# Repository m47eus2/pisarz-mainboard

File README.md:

# pisarz-mainboard
Mainboard for PiSARZ project

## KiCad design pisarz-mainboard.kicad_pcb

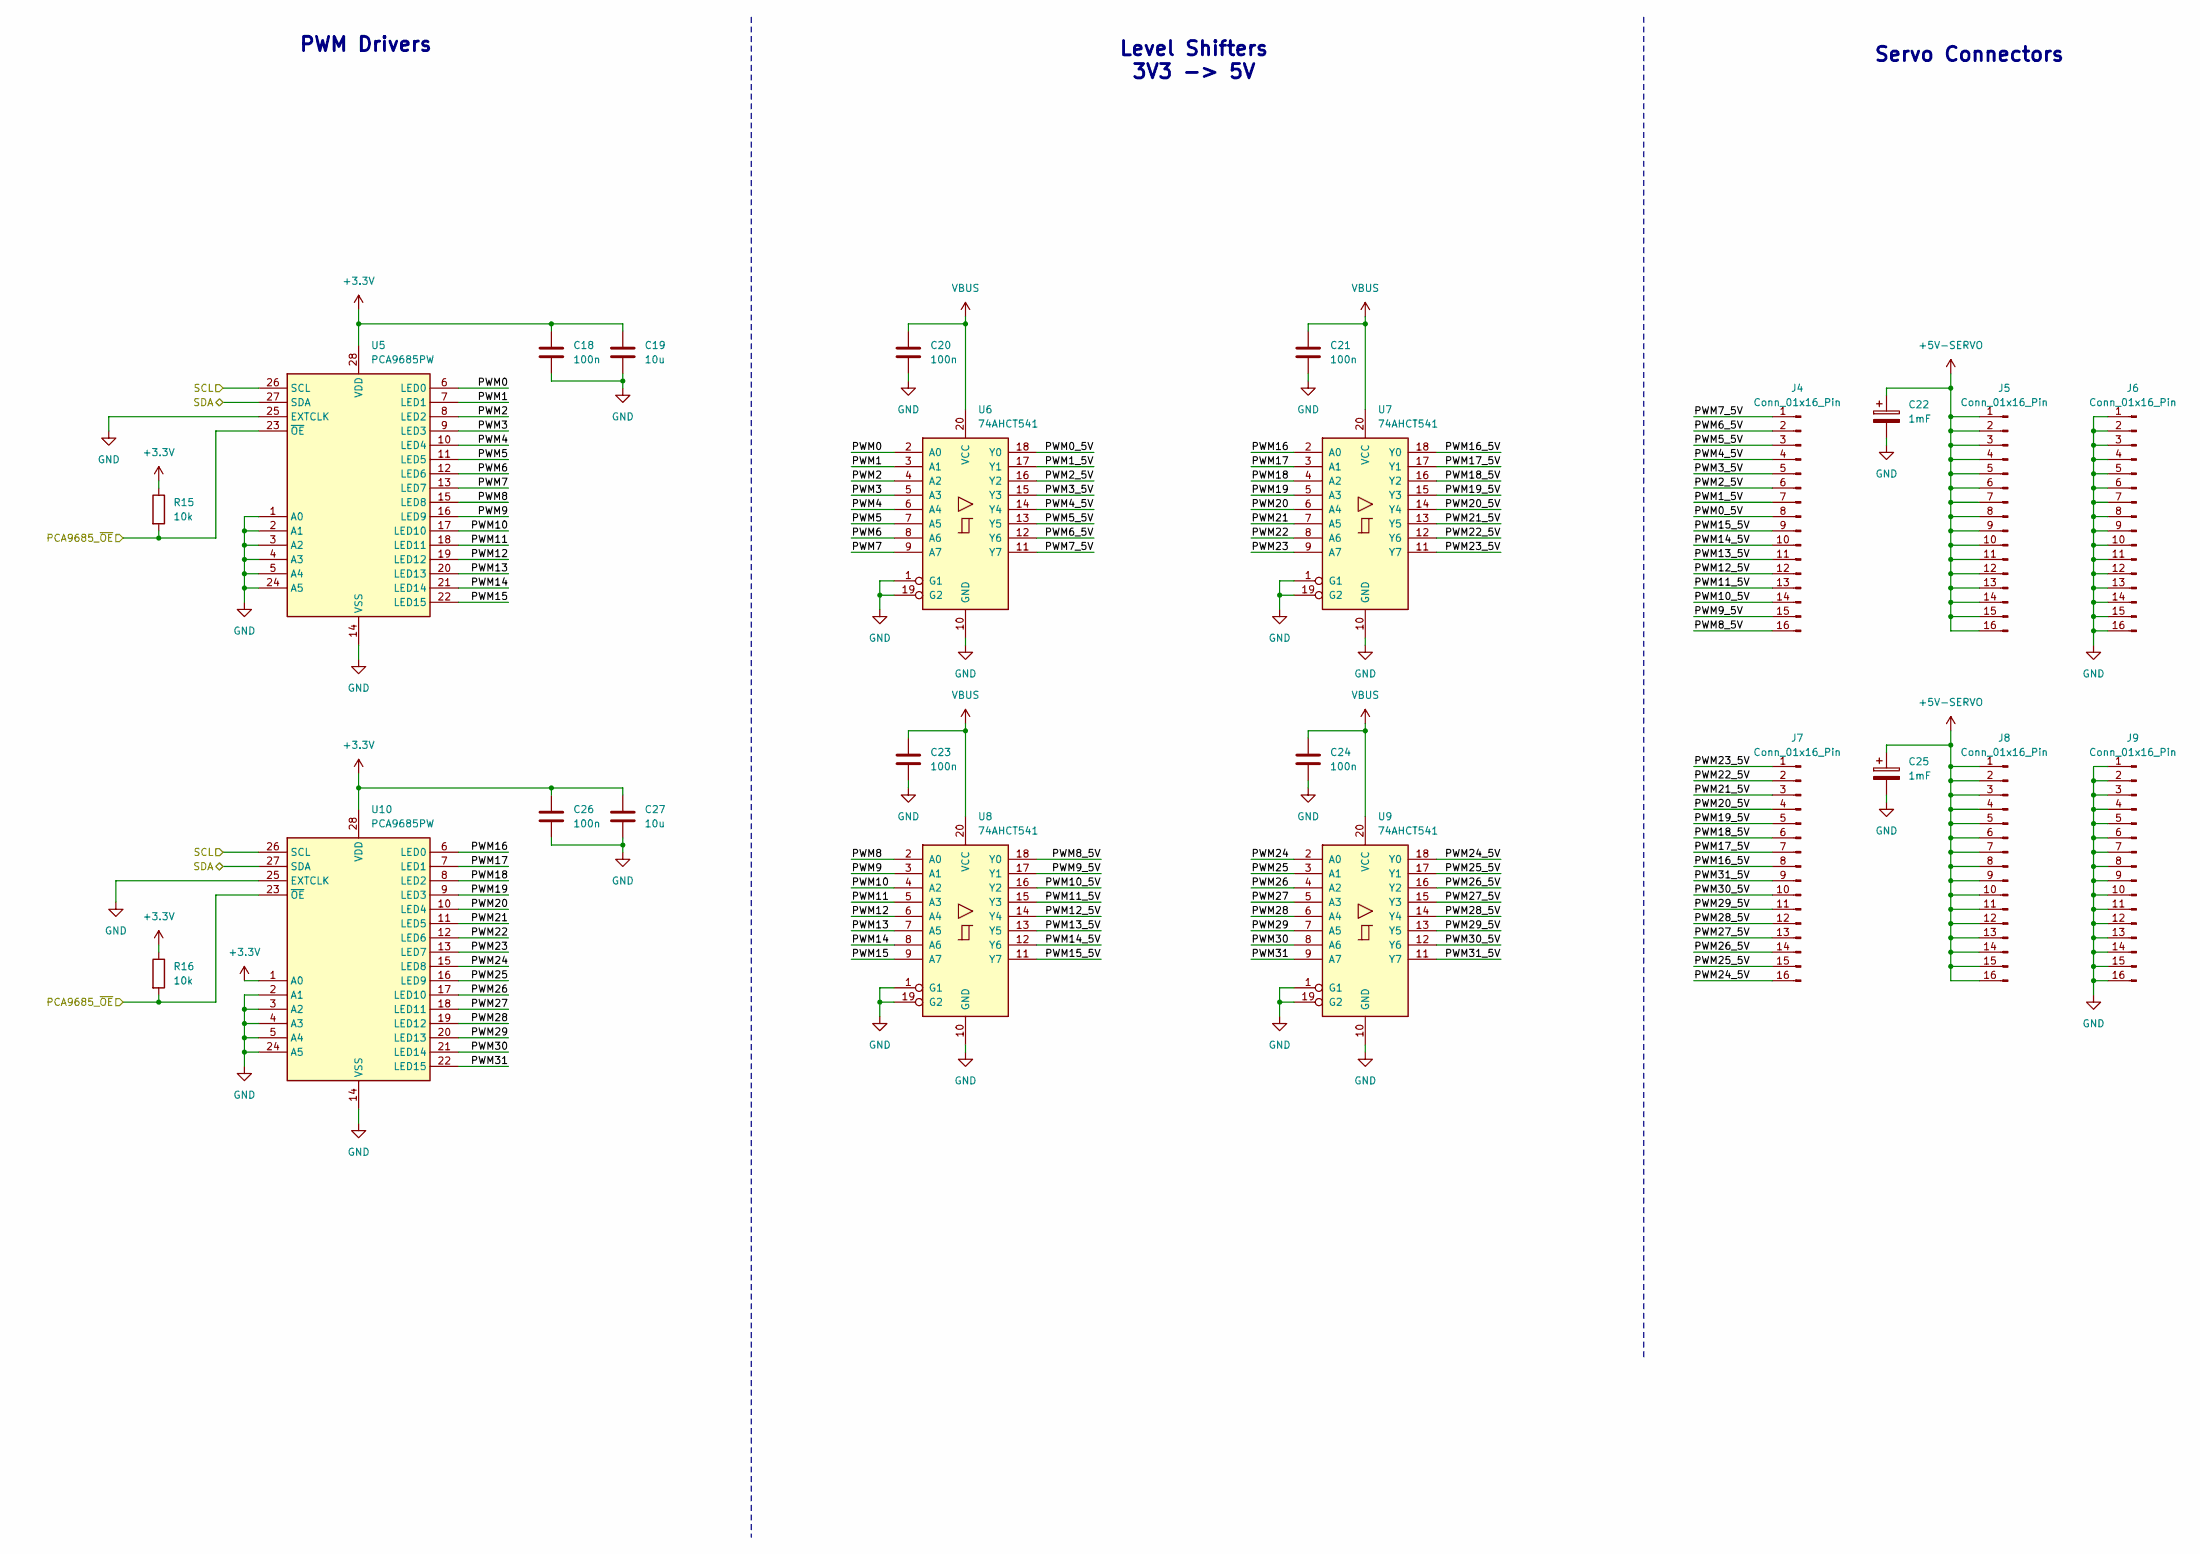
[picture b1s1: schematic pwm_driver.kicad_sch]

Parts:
C18, C20, C21, C23, C24, C26: 100n; C_0402_1005Metric_Pad0.74x0.62mm_HandSolder
C19, C27: 10u; C_0805_2012Metric_Pad1.18x1.45mm_HandSolder
C22, C25: 1mF; CP_Radial_D8.0mm_P3.50mm
J4, J5, J6, J7, J8, J9: Conn_01x16_Pin; PinHeader_1x16_P2.54mm_Vertical
R15, R16: 10k; R_0402_1005Metric_Pad0.72x0.64mm_HandSolder
U5, U10: PCA9685PW; TSSOP-28_4.4x9.7mm_P0.65mm
U6, U7, U8, U9: 74AHCT541; SSOP-20_4.4x6.5mm_P0.65mm

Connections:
+3.3V: C18.1, C19.1, C26.1, C27.1, R15.1, R16.1, U5.28 (VDD), U10.1 (A0), U10.28 (VDD); also elsewhere on the board
+5V-SERVO: C22.1, C25.1, J5.1, J5.2, J5.3, J5.4, J5.5, J5.6, J5.7, J5.8, J5.9, J5.10, J5.11, J5.12, J5.13, J5.14, J5.15, J5.16, J8.1, J8.2, J8.3, J8.4, J8.5, J8.6, J8.7, J8.8, J8.9, J8.10, J8.11, J8.12, J8.13, J8.14, J8.15, J8.16; also elsewhere on the board
/mcu/I2C_SCL: U5.26 (SCL), U10.26 (SCL); also elsewhere on the board
/mcu/I2C_SDA: U5.27 (SDA), U10.27 (SDA); also elsewhere on the board
/mcu/PCA_OE: R15.2, R16.2, U5.23 (~OE), U10.23 (~OE); also elsewhere on the board
/pwm-driver/PWM0: U5.6 (LED0), U6.2 (A0)
/pwm-driver/PWM0_5V: J4.8, U6.18 (Y0)
/pwm-driver/PWM1: U5.7 (LED1), U6.3 (A1)
/pwm-driver/PWM1_5V: J4.7, U6.17 (Y1)
/pwm-driver/PWM2: U5.8 (LED2), U6.4 (A2)
/pwm-driver/PWM2_5V: J4.6, U6.16 (Y2)
/pwm-driver/PWM3: U5.9 (LED3), U6.5 (A3)
/pwm-driver/PWM3_5V: J4.5, U6.15 (Y3)
/pwm-driver/PWM4: U5.10 (LED4), U6.6 (A4)
/pwm-driver/PWM4_5V: J4.4, U6.14 (Y4)
/pwm-driver/PWM5: U5.11 (LED5), U6.7 (A5)
/pwm-driver/PWM5_5V: J4.3, U6.13 (Y5)
/pwm-driver/PWM6: U5.12 (LED6), U6.8 (A6)
/pwm-driver/PWM6_5V: J4.2, U6.12 (Y6)
/pwm-driver/PWM7: U5.13 (LED7), U6.9 (A7)
/pwm-driver/PWM7_5V: J4.1, U6.11 (Y7)
/pwm-driver/PWM8: U5.15 (LED8), U8.2 (A0)
/pwm-driver/PWM8_5V: J4.16, U8.18 (Y0)
/pwm-driver/PWM9: U5.16 (LED9), U8.3 (A1)
/pwm-driver/PWM9_5V: J4.15, U8.17 (Y1)
/pwm-driver/PWM10: U5.17 (LED10), U8.4 (A2)
/pwm-driver/PWM10_5V: J4.14, U8.16 (Y2)
/pwm-driver/PWM11: U5.18 (LED11), U8.5 (A3)
/pwm-driver/PWM11_5V: J4.13, U8.15 (Y3)
/pwm-driver/PWM12: U5.19 (LED12), U8.6 (A4)
/pwm-driver/PWM12_5V: J4.12, U8.14 (Y4)
/pwm-driver/PWM13: U5.20 (LED13), U8.7 (A5)
/pwm-driver/PWM13_5V: J4.11, U8.13 (Y5)
/pwm-driver/PWM14: U5.21 (LED14), U8.8 (A6)
/pwm-driver/PWM14_5V: J4.10, U8.12 (Y6)
/pwm-driver/PWM15: U5.22 (LED15), U8.9 (A7)
/pwm-driver/PWM15_5V: J4.9, U8.11 (Y7)
/pwm-driver/PWM16: U7.2 (A0), U10.6 (LED0)
/pwm-driver/PWM16_5V: J7.8, U7.18 (Y0)
/pwm-driver/PWM17: U7.3 (A1), U10.7 (LED1)
/pwm-driver/PWM17_5V: J7.7, U7.17 (Y1)
/pwm-driver/PWM18: U7.4 (A2), U10.8 (LED2)
/pwm-driver/PWM18_5V: J7.6, U7.16 (Y2)
/pwm-driver/PWM19: U7.5 (A3), U10.9 (LED3)
/pwm-driver/PWM19_5V: J7.5, U7.15 (Y3)
/pwm-driver/PWM20: U7.6 (A4), U10.10 (LED4)
/pwm-driver/PWM20_5V: J7.4, U7.14 (Y4)
/pwm-driver/PWM21: U7.7 (A5), U10.11 (LED5)
/pwm-driver/PWM21_5V: J7.3, U7.13 (Y5)
/pwm-driver/PWM22: U7.8 (A6), U10.12 (LED6)
/pwm-driver/PWM22_5V: J7.2, U7.12 (Y6)
/pwm-driver/PWM23: U7.9 (A7), U10.13 (LED7)
/pwm-driver/PWM23_5V: J7.1, U7.11 (Y7)
/pwm-driver/PWM24: U9.2 (A0), U10.15 (LED8)
/pwm-driver/PWM24_5V: J7.16, U9.18 (Y0)
/pwm-driver/PWM25: U9.3 (A1), U10.16 (LED9)
/pwm-driver/PWM25_5V: J7.15, U9.17 (Y1)
/pwm-driver/PWM26: U9.4 (A2), U10.17 (LED10)
/pwm-driver/PWM26_5V: J7.14, U9.16 (Y2)
/pwm-driver/PWM27: U9.5 (A3), U10.18 (LED11)
/pwm-driver/PWM27_5V: J7.13, U9.15 (Y3)
/pwm-driver/PWM28: U9.6 (A4), U10.19 (LED12)
/pwm-driver/PWM28_5V: J7.12, U9.14 (Y4)
/pwm-driver/PWM29: U9.7 (A5), U10.20 (LED13)
/pwm-driver/PWM29_5V: J7.11, U9.13 (Y5)
/pwm-driver/PWM30: U9.8 (A6), U10.21 (LED14)
/pwm-driver/PWM30_5V: J7.10, U9.12 (Y6)
/pwm-driver/PWM31: U9.9 (A7), U10.22 (LED15)
/pwm-driver/PWM31_5V: J7.9, U9.11 (Y7)
GND: C18.2, C19.2, C20.2, C21.2, C22.2, C23.2, C24.2, C25.2, C26.2, C27.2, J6.1, J6.2, J6.3, J6.4, J6.5, J6.6, J6.7, J6.8, J6.9, J6.10, J6.11, J6.12, J6.13, J6.14, J6.15, J6.16, J9.1, J9.2, J9.3, J9.4, J9.5, J9.6, J9.7, J9.8, J9.9, J9.10, J9.11, J9.12, J9.13, J9.14, J9.15, J9.16, U5.1 (A0), U5.2 (A1), U5.3 (A2), U5.4 (A3), U5.5 (A4), U5.14 (VSS), U5.24 (A5), U5.25 (EXTCLK), U6.1 (G1), U6.10 (GND), U6.19 (G2), U7.1 (G1), U7.10 (GND), U7.19 (G2), U8.1 (G1), U8.10 (GND), U8.19 (G2), U9.1 (G1), U9.10 (GND), U9.19 (G2), U10.2 (A1), U10.3 (A2), U10.4 (A3), U10.5 (A4), U10.14 (VSS), U10.24 (A5), U10.25 (EXTCLK); also elsewhere on the board
VBUS: C20.1, C21.1, C23.1, C24.1, U6.20 (VCC), U7.20 (VCC), U8.20 (VCC), U9.20 (VCC); also elsewhere on the board

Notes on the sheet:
Level Shifters 3V3 -> 5V
PWM Drivers
Servo Connectors

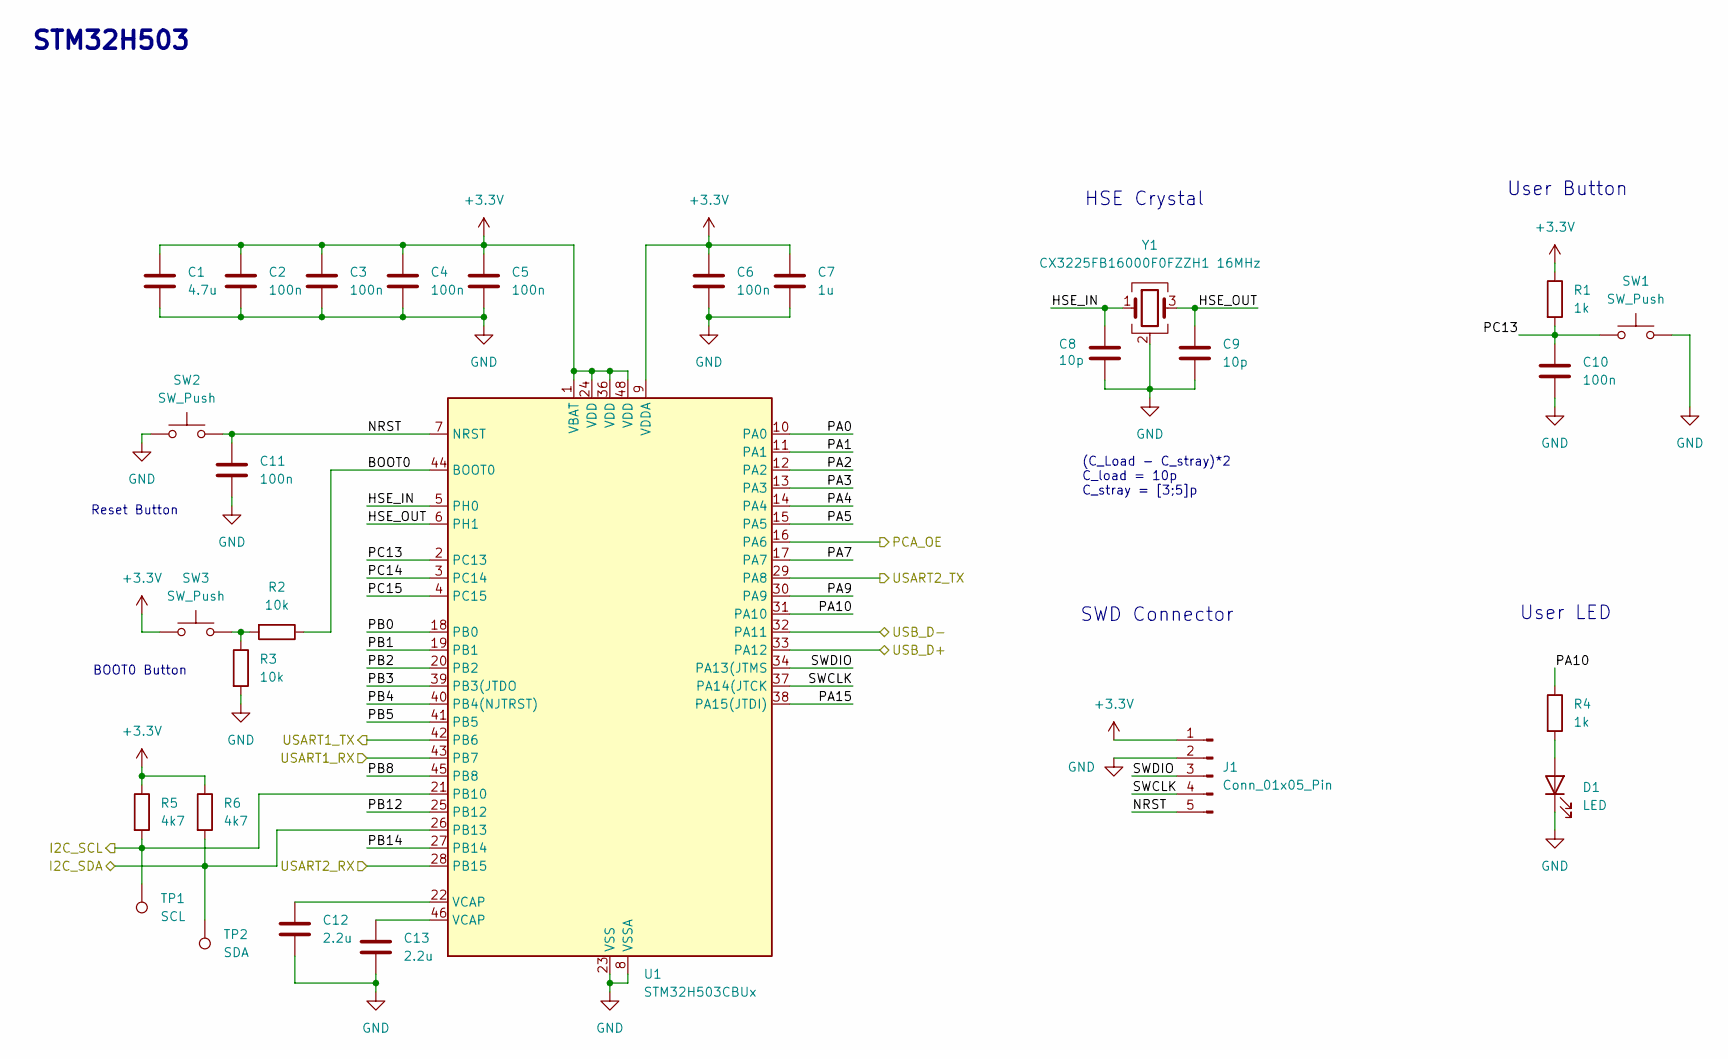
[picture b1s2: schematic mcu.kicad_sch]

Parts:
C1: 4.7u; C_0805_2012Metric_Pad1.18x1.45mm_HandSolder
C2, C3, C4, C5, C6, C10, C11: 100n; C_0402_1005Metric_Pad0.74x0.62mm_HandSolder
C7: 1u; C_0603_1608Metric_Pad1.08x0.95mm_HandSolder
C8, C9: 10p; C_0402_1005Metric_Pad0.74x0.62mm_HandSolder
C12, C13: 2.2u; C_0603_1608Metric_Pad1.08x0.95mm_HandSolder
D1: LED; LED_0805_2012Metric_Pad1.15x1.40mm_HandSolder
J1: Conn_01x05_Pin; PinHeader_1x05_P2.54mm_Vertical
R1, R4: 1k; R_0402_1005Metric_Pad0.72x0.64mm_HandSolder
R2, R3: 10k; R_0402_1005Metric_Pad0.72x0.64mm_HandSolder
R5, R6: 4k7; R_0402_1005Metric_Pad0.72x0.64mm_HandSolder
SW1, SW2, SW3: SW_Push; SW_Push_1P1T_NO_E-Switch_TL3301NxxxxxG
TP1: SCL; TestPoint_Pad_D1.0mm
TP2: SDA; TestPoint_Pad_D1.0mm
U1: STM32H503CBUx; QFN-48-1EP_7x7mm_P0.5mm_EP5.6x5.6mm
Y1: CX3225FB16000F0FZZH1 16MHz; Crystal_SMD_3225-4Pin_3.2x2.5mm

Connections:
+3.3V: C1.1, C2.1, C3.1, C4.1, C5.1, C6.1, C7.1, J1.1, R1.1, R5.1, R6.1, SW3.1, U1.1 (VBAT), U1.9 (VDDA), U1.24 (VDD), U1.36 (VDD), U1.48 (VDD); also elsewhere on the board
/esp32-module-connector/esp32_RX: U1.42 (PB6); also elsewhere on the board
/esp32-module-connector/esp32_TX: U1.43 (PB7); also elsewhere on the board
/mcu/BOOT0: R2.1, U1.44 (BOOT0)
/mcu/HSE_IN: C8.1, U1.5 (PH0), Y1.1
/mcu/HSE_OUT: C9.1, U1.6 (PH1), Y1.3
/mcu/I2C_SCL: R5.2, TP1.1 (1_1), U1.21 (PB10); also elsewhere on the board
/mcu/I2C_SDA: R6.2, TP2.1 (1_1), U1.26 (PB13); also elsewhere on the board
/mcu/NRST: C11.1, J1.5, SW2.2, U1.7 (NRST)
/mcu/PA0: U1.10 (PA0)
/mcu/PA1: U1.11 (PA1)
/mcu/PA2: U1.12 (PA2)
/mcu/PA3: U1.13 (PA3)
/mcu/PA4: U1.14 (PA4)
/mcu/PA5: U1.15 (PA5)
/mcu/PA7: U1.17 (PA7)
/mcu/PA9: U1.30 (PA9)
/mcu/PA10: R4.1, U1.31 (PA10)
/mcu/PA15: U1.38 (PA15(JTDI))
/mcu/PB0: U1.18 (PB0)
/mcu/PB1: U1.19 (PB1)
/mcu/PB2: U1.20 (PB2)
/mcu/PB3: U1.39 (PB3(JTDO)
/mcu/PB4: U1.40 (PB4(NJTRST))
/mcu/PB5: U1.41 (PB5)
/mcu/PB8: U1.45 (PB8)
/mcu/PB12: U1.25 (PB12)
/mcu/PB14: U1.27 (PB14)
/mcu/PC13: C10.1, R1.2, SW1.1, U1.2 (PC13)
/mcu/PC14: U1.3 (PC14)
/mcu/PC15: U1.4 (PC15)
/mcu/PCA_OE: U1.16 (PA6); also elsewhere on the board
/mcu/SWCLK: J1.4, U1.37 (PA14(JTCK)
/mcu/SWDIO: J1.3, U1.34 (PA13(JTMS)
/mcu/USART2_RX: U1.28 (PB15); also elsewhere on the board
/mcu/USART2_TX: U1.29 (PA8); also elsewhere on the board
/mcu/USB_D+: U1.33 (PA12); also elsewhere on the board
/mcu/USB_D-: U1.32 (PA11); also elsewhere on the board
GND: C1.2, C2.2, C3.2, C4.2, C5.2, C6.2, C7.2, C8.2, C9.2, C10.2, C11.2, C12.2, C13.2, D1.1 (K), J1.2, R3.2, SW1.2, SW2.1, U1.8 (VSSA), U1.23 (VSS), U1.35 (VSS), U1.47 (VSS), U1.49 (VSS), Y1.2 (G), Y1.4 (G); also elsewhere on the board
unnamed: C12.1, U1.22 (VCAP)
unnamed: C13.1, U1.46 (VCAP)
unnamed: D1.2 (A), R4.2
unnamed: R2.2, R3.1, SW3.2

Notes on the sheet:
SWD Connector
User Button
HSE Crystal
Reset Button
(C_Load - C_stray)*2 C_load = 10p C_stray = [3;5]p
STM32H503
User LED
BOOT0 Button

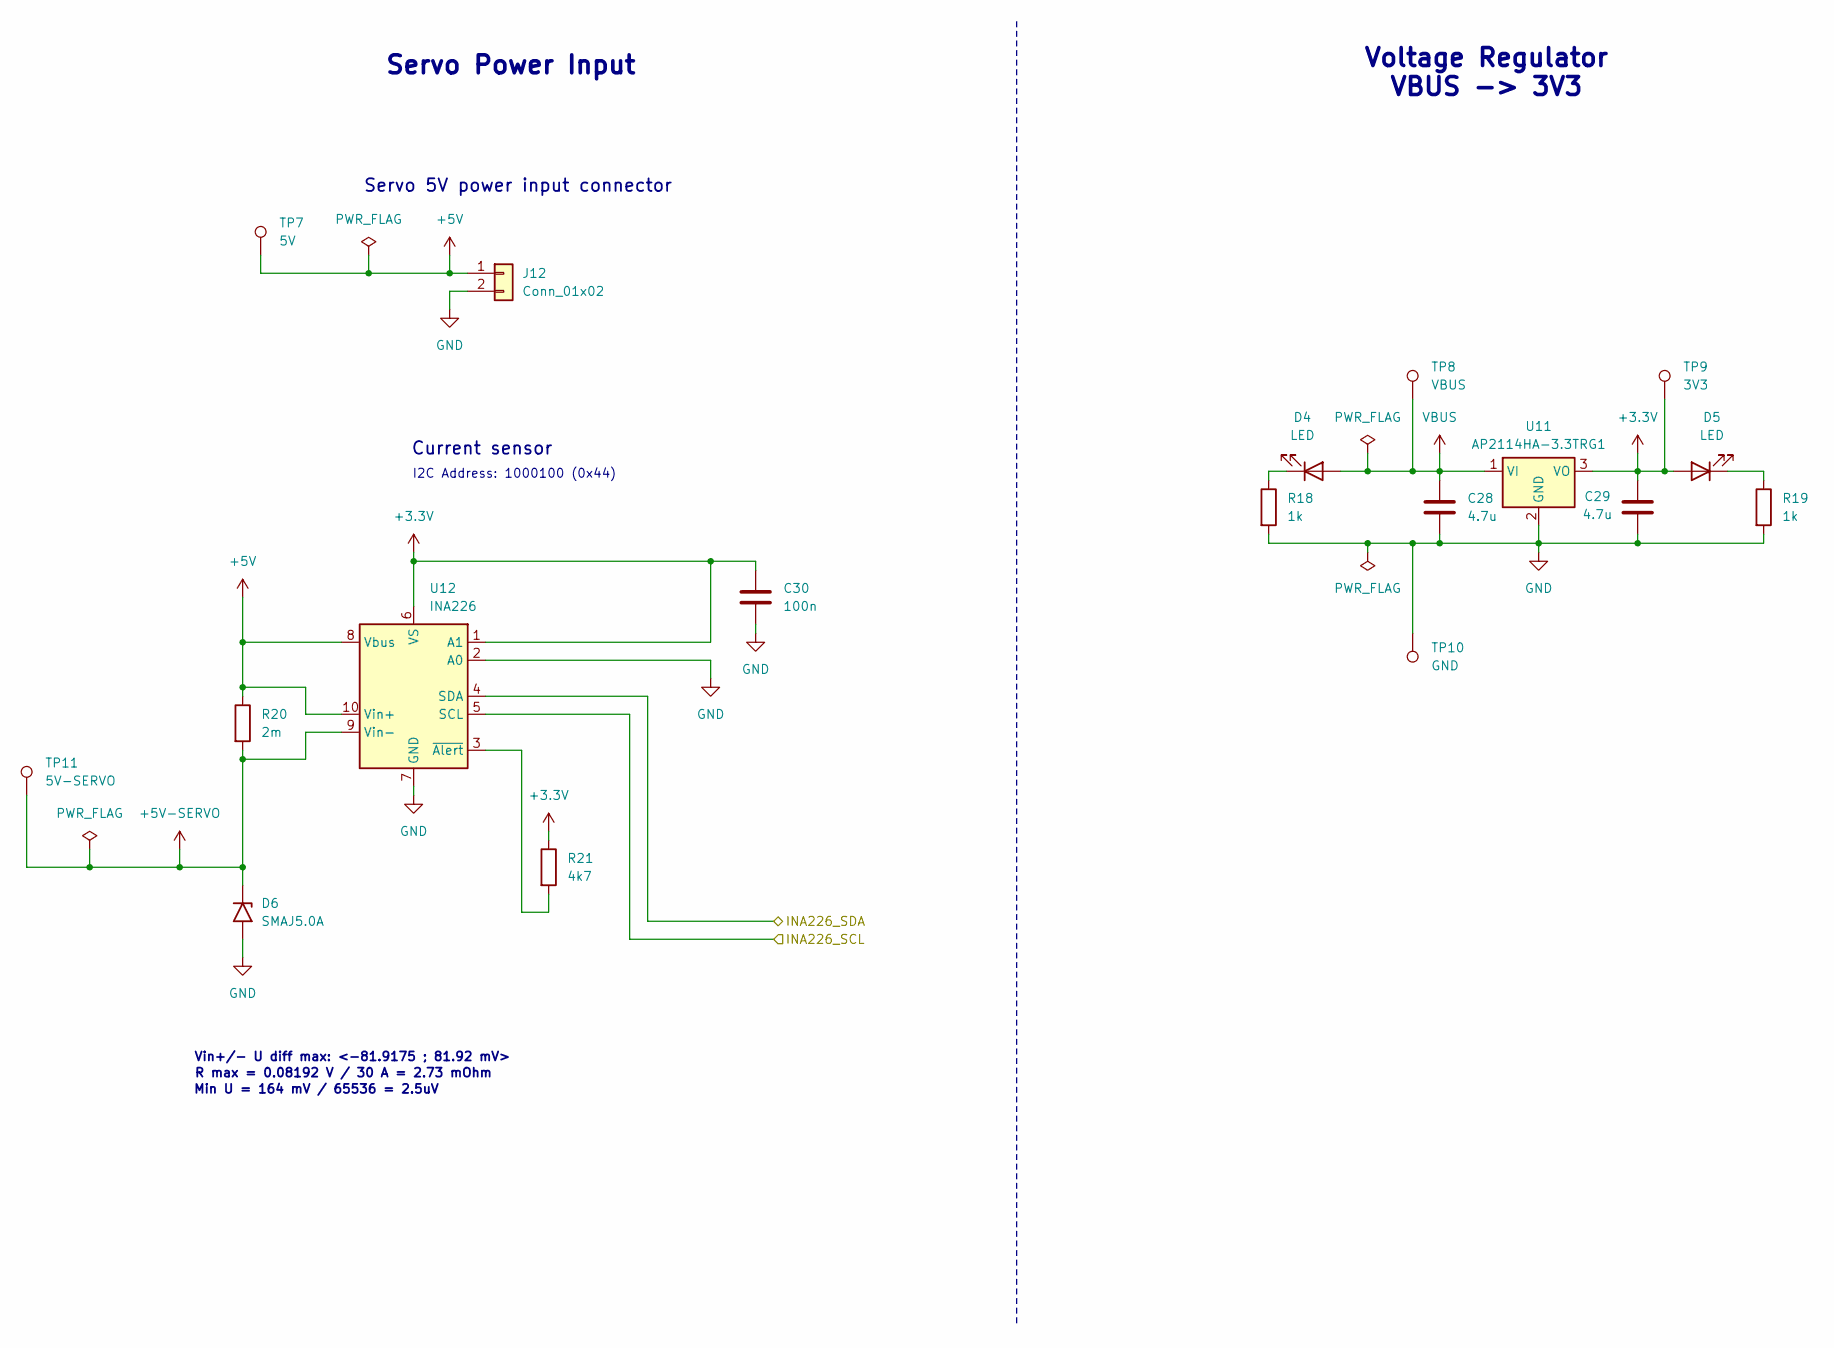
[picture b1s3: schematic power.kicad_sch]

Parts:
C28, C29: 4.7u; C_0805_2012Metric_Pad1.18x1.45mm_HandSolder
C30: 100n; C_0402_1005Metric_Pad0.74x0.62mm_HandSolder
D4, D5: LED; LED_0805_2012Metric_Pad1.15x1.40mm_HandSolder
D6: SMAJ5.0A; D_SMA
J12: Conn_01x02; TerminalBlock_Phoenix_MKDS-1,5-2_1x02_P5.00mm_Horizontal
R18, R19: 1k; R_0402_1005Metric_Pad0.72x0.64mm_HandSolder
R20: 2m; R_2512_6332Metric_Pad1.40x3.35mm_HandSolder
R21: 4k7; R_0402_1005Metric_Pad0.72x0.64mm_HandSolder
TP7: 5V; TestPoint_Pad_D1.0mm
TP8: VBUS; TestPoint_Pad_D1.0mm
TP9: 3V3; TestPoint_Pad_D1.0mm
TP10: GND; TestPoint_Pad_D1.0mm
TP11: 5V-SERVO; TestPoint_Pad_D1.0mm
U11: AP2114HA-3.3TRG1; SOT-223-3_TabPin2
U12: INA226; TSSOP-10_3x3mm_P0.5mm

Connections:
+3.3V: C29.1, C30.1, D5.2 (A), R21.1, TP9.1 (1_1), U11.3 (VO), U12.1 (A1), U12.6 (VS); also elsewhere on the board
+5V: J12.1, R20.1, TP7.1 (1_1), U12.8 (Vbus), U12.10 (Vin+)
+5V-SERVO: D6.1 (A1), R20.2, TP11.1 (1_1), U12.9 (Vin-); also elsewhere on the board
/mcu/I2C_SCL: U12.5 (SCL); also elsewhere on the board
/mcu/I2C_SDA: U12.4 (SDA); also elsewhere on the board
GND: C28.2, C29.2, C30.2, D6.2 (A2), J12.2, R18.2, R19.2, TP10.1 (1_1), U11.2 (GND), U12.2 (A0), U12.7 (GND); also elsewhere on the board
unnamed: D4.1 (K), R18.1
unnamed: D5.1 (K), R19.1
unnamed: R21.2, U12.3 (~Alert)
VBUS: C28.1, D4.2 (A), TP8.1 (1_1), U11.1 (VI); also elsewhere on the board

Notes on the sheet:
Vin+/- U diff max: <-81.9175 ; 81.92 mV>
Current sensor
Voltage Regulator VBUS -> 3V3
Min U = 164 mV / 65536 = 2.5uV
R max = 0.08192 V / 30 A = 2.73 mOhm
Servo Power Input
Servo 5V power input connector
I2C Address: 1000100 (0x44)

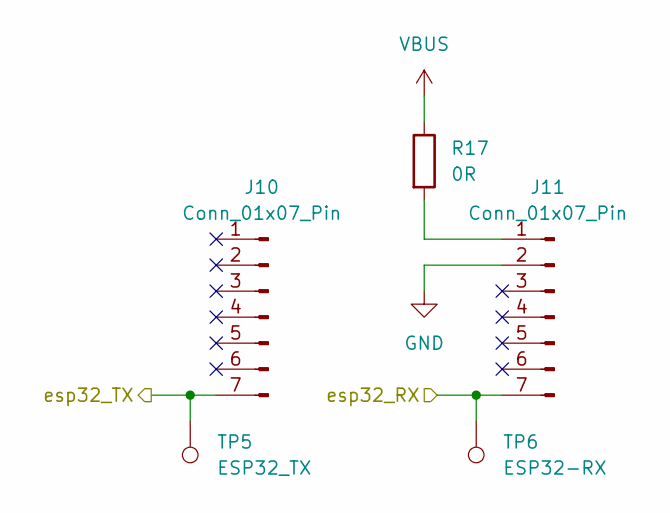
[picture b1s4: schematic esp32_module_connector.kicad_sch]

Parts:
J10, J11: Conn_01x07_Pin; PinHeader_1x07_P2.54mm_Vertical
R17: 0R; R_0402_1005Metric_Pad0.72x0.64mm_HandSolder
TP5: ESP32_TX; TestPoint_Pad_D1.0mm
TP6: ESP32-RX; TestPoint_Pad_D1.0mm

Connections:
/esp32-module-connector/esp32_RX: J11.7, TP6.1 (1_1); also elsewhere on the board
/esp32-module-connector/esp32_TX: J10.7 (Pin_7_7), TP5.1 (1_1); also elsewhere on the board
GND: J11.2; also elsewhere on the board
unnamed: J11.1, R17.2
VBUS: R17.1; also elsewhere on the board

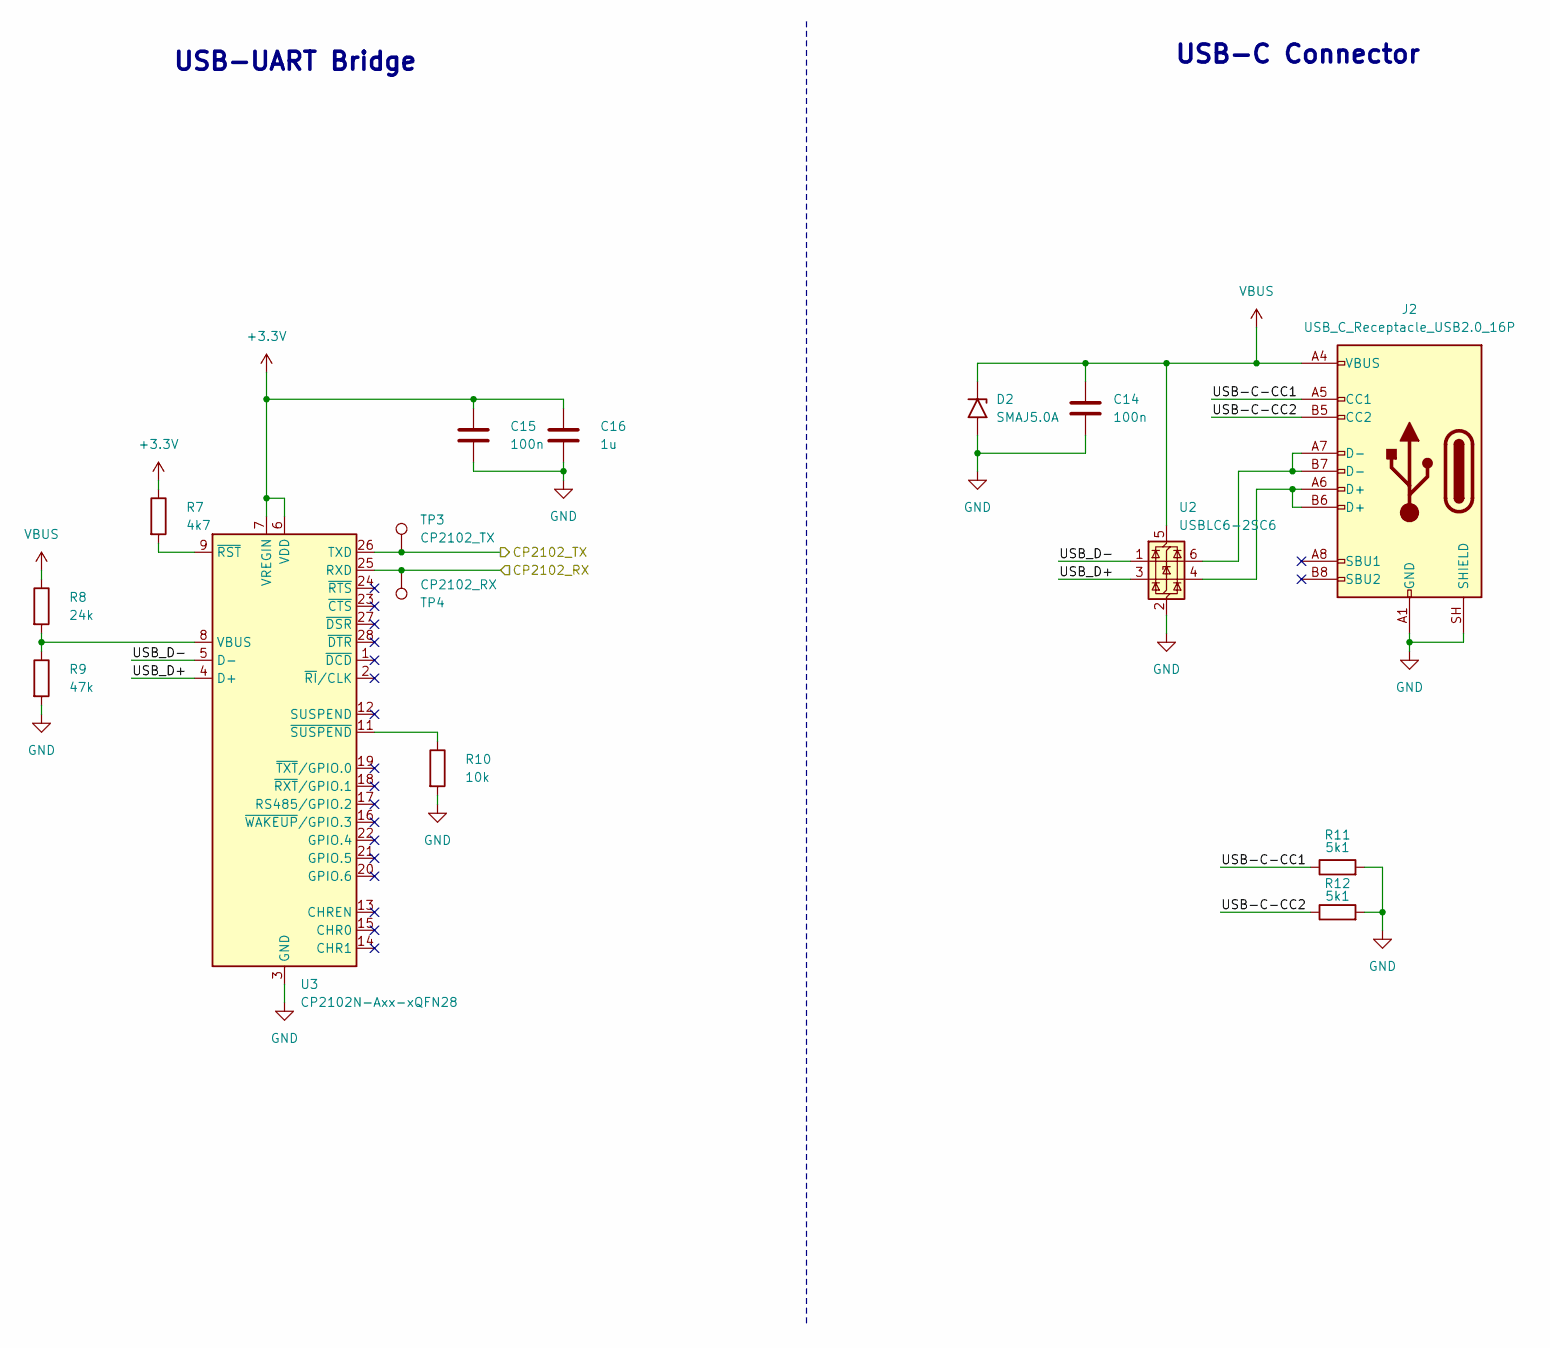
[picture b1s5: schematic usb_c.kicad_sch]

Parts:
C14, C15: 100n; C_0402_1005Metric_Pad0.74x0.62mm_HandSolder
C16: 1u; C_0603_1608Metric_Pad1.08x0.95mm_HandSolder
D2: SMAJ5.0A; D_SMA
J2: USB_C_Receptacle_USB2.0_16P; USB_C_Receptacle_GCT_USB4105-xx-A_16P_TopMnt_Horizontal
R7: 4k7; R_0402_1005Metric_Pad0.72x0.64mm_HandSolder
R8: 24k; R_0402_1005Metric_Pad0.72x0.64mm_HandSolder
R9: 47k; R_0402_1005Metric_Pad0.72x0.64mm_HandSolder
R10: 10k; R_0402_1005Metric_Pad0.72x0.64mm_HandSolder
R11, R12: 5k1; R_0402_1005Metric_Pad0.72x0.64mm_HandSolder
TP3: CP2102_TX; TestPoint_Pad_D1.0mm
TP4: CP2102_RX; TestPoint_Pad_D1.0mm
U2: USBLC6-2SC6; SOT-23-6
U3: CP2102N-Axx-xQFN28; QFN-28-1EP_5x5mm_P0.5mm_EP3.35x3.35mm

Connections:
+3.3V: C15.1, C16.1, R7.1, U3.6 (VDD), U3.7 (VREGIN); also elsewhere on the board
/mcu/USART2_RX: TP3.1 (1_1), U3.26 (TXD); also elsewhere on the board
/mcu/USART2_TX: TP4.1 (1_1), U3.25 (RXD); also elsewhere on the board
/usb-c/USB-C-CC1: J2.A5 (CC1), R11.1
/usb-c/USB-C-CC2: J2.B5 (CC2), R12.1
/usb-c/USB_D+: U2.3 (I/O2), U3.4 (D+)
/usb-c/USB_D-: U2.1 (I/O1), U3.5 (D-)
GND: C14.2, C15.2, C16.2, D2.2 (A2), J2.A1 (GND), J2.A12 (GND), J2.B1 (GND), J2.B12 (GND), J2.SH (SHIELD), R9.2, R10.2, R11.2, R12.2, U2.2 (GND), U3.3 (GND), U3.29 (GND); also elsewhere on the board
unnamed: J2.A6 (D+), J2.B6 (D+), U2.4 (I/O2)
unnamed: J2.A7 (D-), J2.B7 (D-), U2.6 (I/O1)
unnamed: R8.2, R9.1, U3.8 (VBUS)
unnamed: R7.2, U3.9 (~RST)
unnamed: R10.1, U3.11 (~SUSPEND)
VBUS: C14.1, D2.1 (A1), J2.A4 (VBUS), J2.A9 (VBUS), J2.B4 (VBUS), J2.B9 (VBUS), R8.1, U2.5 (VBUS); also elsewhere on the board

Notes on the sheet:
USB-UART Bridge
USB-C Connector

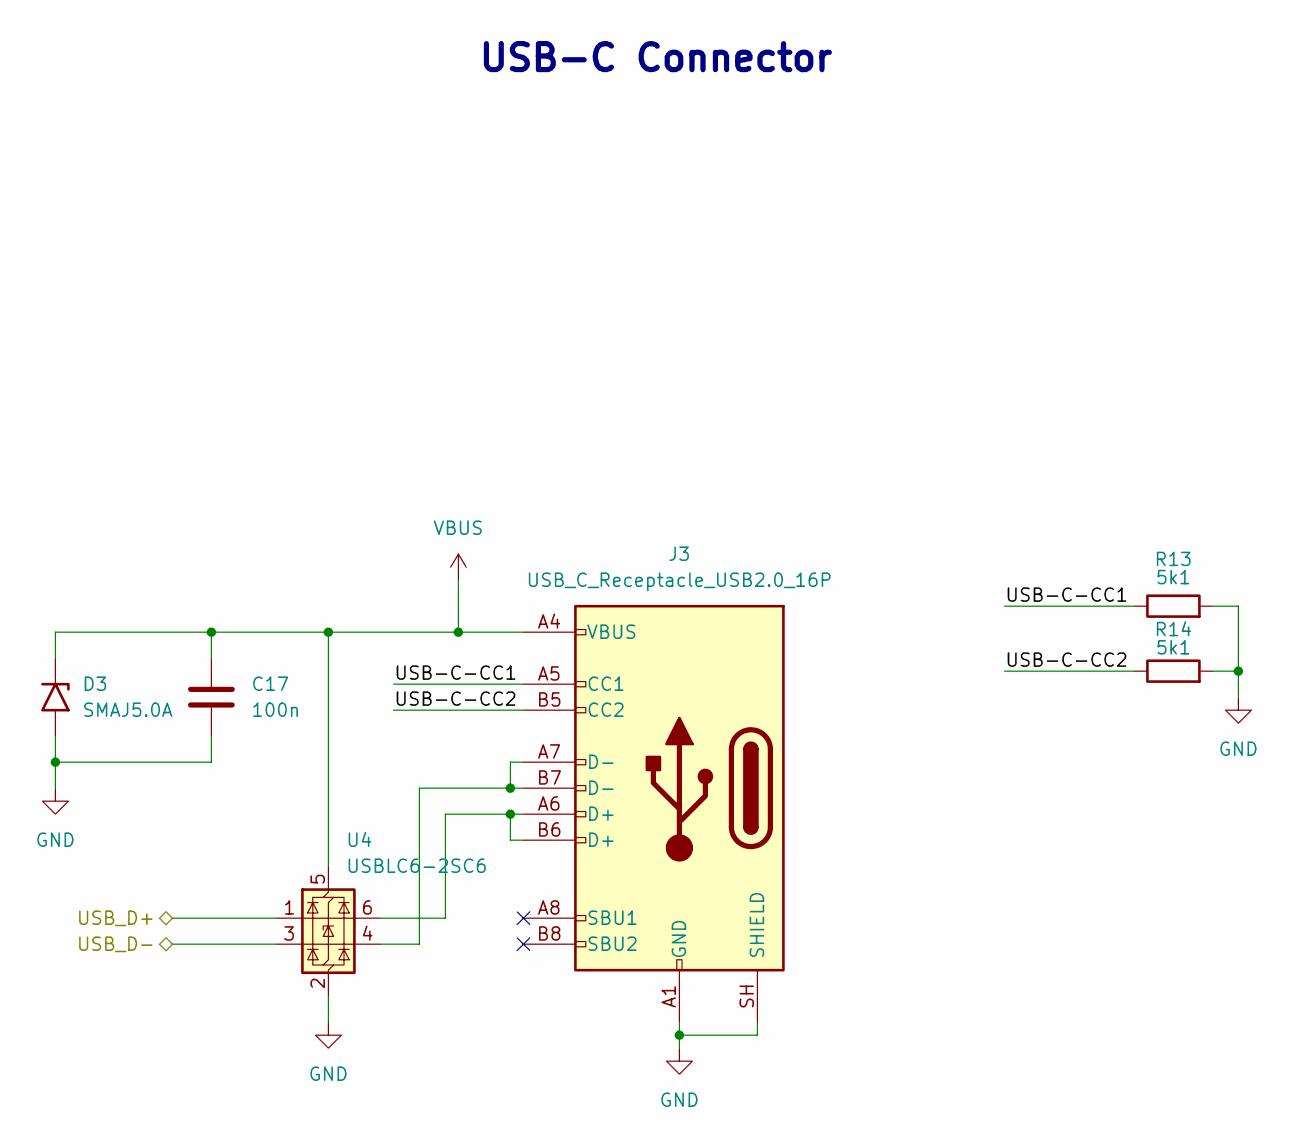
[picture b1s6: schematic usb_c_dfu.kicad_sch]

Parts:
C17: 100n; C_0402_1005Metric_Pad0.74x0.62mm_HandSolder
D3: SMAJ5.0A; D_SMA
J3: USB_C_Receptacle_USB2.0_16P; USB_C_Receptacle_GCT_USB4105-xx-A_16P_TopMnt_Horizontal
R13, R14: 5k1; R_0402_1005Metric_Pad0.72x0.64mm_HandSolder
U4: USBLC6-2SC6; SOT-23-6

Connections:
/mcu/USB_D+: U4.1 (I/O1); also elsewhere on the board
/mcu/USB_D-: U4.3 (I/O2); also elsewhere on the board
/usb-c-dfu/USB-C-CC1: J3.A5 (CC1), R13.1
/usb-c-dfu/USB-C-CC2: J3.B5 (CC2), R14.1
GND: C17.2, D3.2 (A2), J3.A1 (GND), J3.A12 (GND), J3.B1 (GND), J3.B12 (GND), J3.SH (SHIELD), R13.2, R14.2, U4.2 (GND); also elsewhere on the board
unnamed: J3.A6 (D+), J3.B6 (D+), U4.6 (I/O1)
unnamed: J3.A7 (D-), J3.B7 (D-), U4.4 (I/O2)
VBUS: C17.1, D3.1 (A1), J3.A4 (VBUS), J3.A9 (VBUS), J3.B4 (VBUS), J3.B9 (VBUS), U4.5 (VBUS); also elsewhere on the board

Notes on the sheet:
USB-C Connector

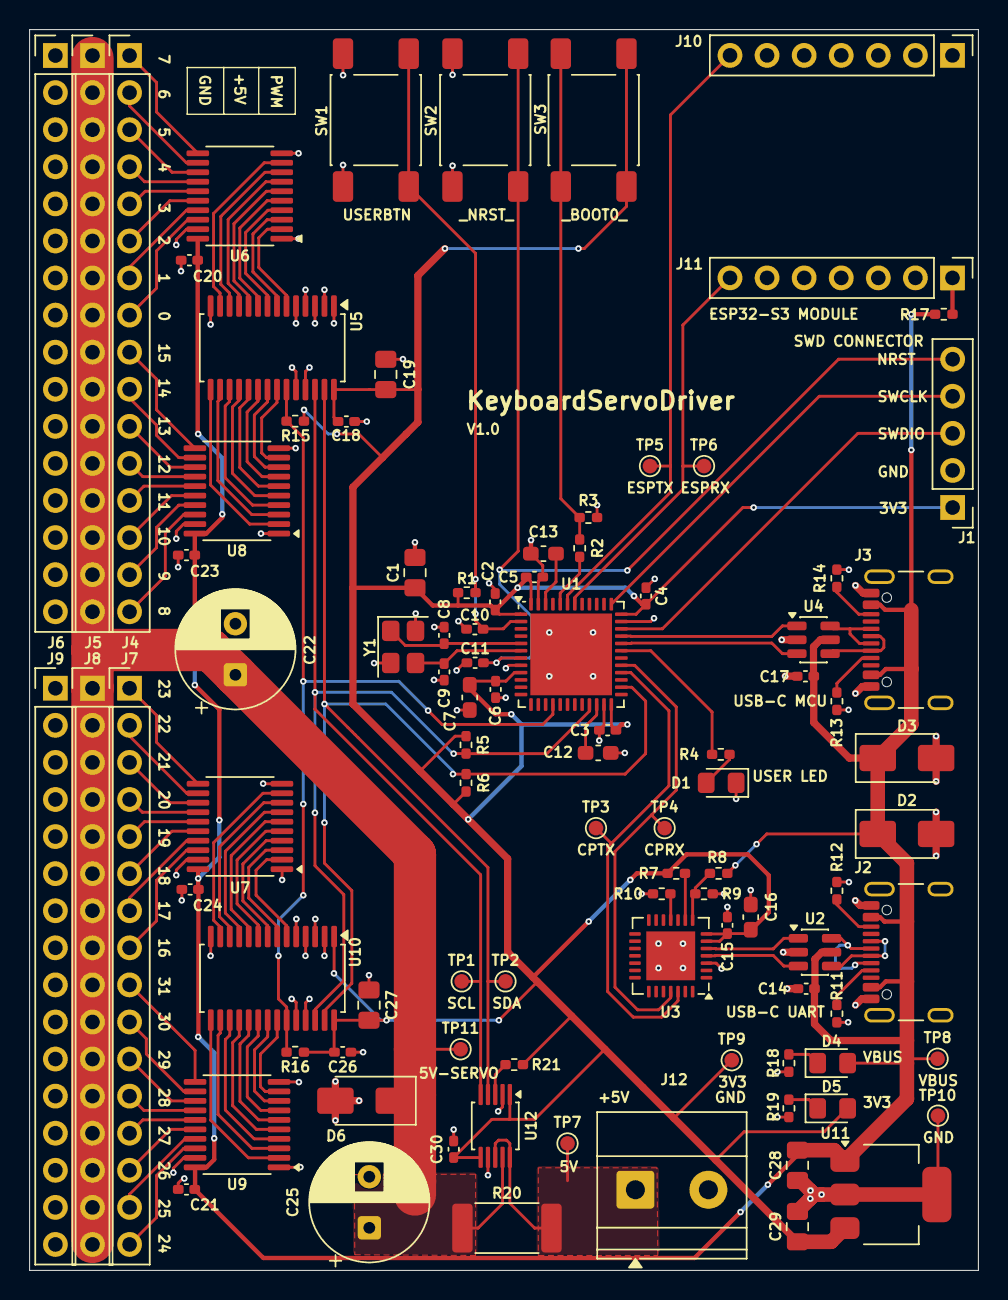
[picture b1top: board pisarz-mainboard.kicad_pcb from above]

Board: 2 copper layers, 65.0 x 85.0 mm, 96 parts (0 on the bottom side), 107 nets.
